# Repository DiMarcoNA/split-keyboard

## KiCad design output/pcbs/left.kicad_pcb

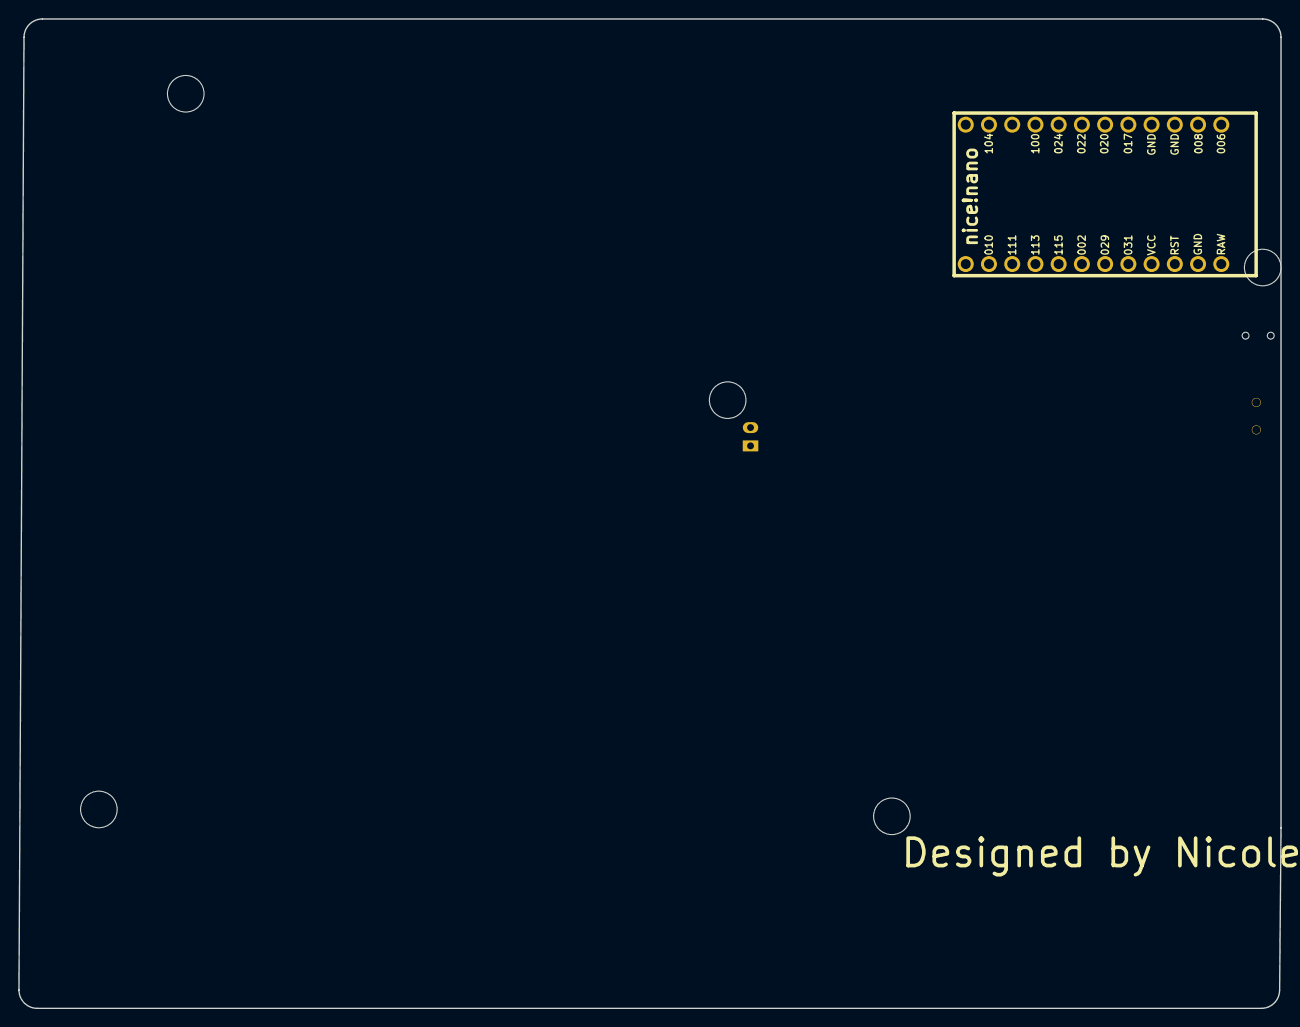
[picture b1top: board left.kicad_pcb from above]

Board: 2 copper layers, 138.0 x 108.2 mm, 4 parts (0 on the bottom side), 4 nets, no tracks yet.

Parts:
B1: Panasonic_EVQPUL_EVQPUC
JST1: JST_PH_S2B-PH-K_02x2.00mm_Angled
MCU1: nice_nano
T1: SPDT_C128955

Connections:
GND: B1.1, JST1.2, MCU1.3, MCU1.4, MCU1.23
RAW: MCU1.24, T1.2
RST: B1.2, MCU1.22
pos: JST1.1, T1.1

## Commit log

2026-01-02 initial commit with initial design
2026-01-04 naming conventions, make it readable to ergogen
2026-01-04 some readability changes, some stylistic comments, redo board outlines to be square for aesthetic reasons. also including key outlines in board outlines for clarity and sanity checking that will be d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
2026-01-04 final board outlines
2026-01-05 final plate outlines, includes sanity check keys but those will be deleted in later commit
2026-01-05 reorganized to follow ergogen formatting. Added footprints for componenets on board that arent native to ergogen
2026-06-22 file structure changes
2026-06-23 first ergogen run to test pcb
2026-06-23 trying to place ts, not working. hotswap not showing up
